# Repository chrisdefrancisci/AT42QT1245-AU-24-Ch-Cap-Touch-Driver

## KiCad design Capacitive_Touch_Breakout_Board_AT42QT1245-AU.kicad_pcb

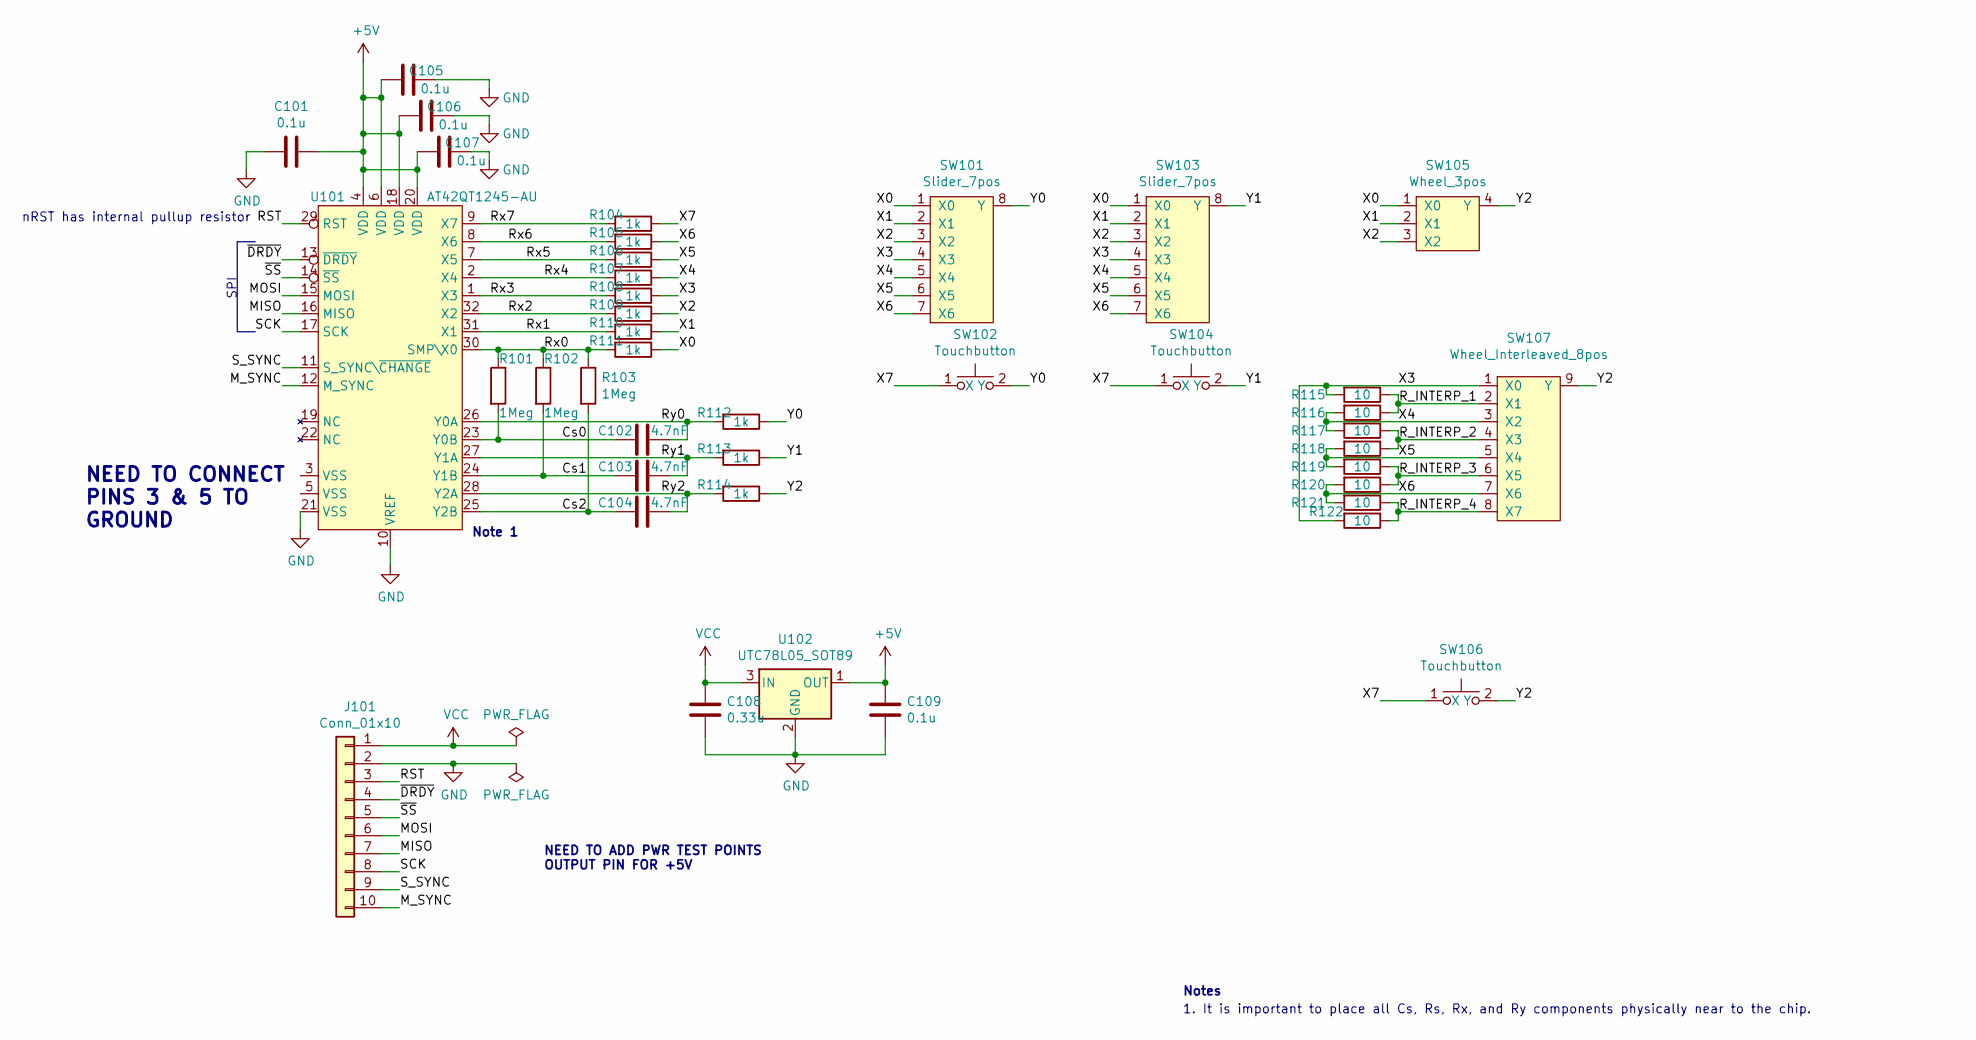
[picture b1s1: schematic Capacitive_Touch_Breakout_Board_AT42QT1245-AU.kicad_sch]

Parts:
C101, C105, C106, C107, C109: 0.1u; C_0402_1005Metric; JLCPCB Part # C307331
C102, C103, C104: 4.7nF; C_0402_1005Metric; JLCPCB Part # C1538
C108: 0.33u; C_0805_2012Metric; JLCPCB Part # C1740
J101: Conn_01x10; PinHeader_1x10_P2.54mm_Vertical
R101, R102, R103: 1Meg; R_0402_1005Metric; JLCPCB Part # C26083
R104, R105, R106, R107, R108, R109, R110, R111, R112, R113, R114: 1k; R_0402_1005Metric; JLCPCB Part # C11702
R115, R116, R117, R118, R119, R120, R121, R122: 10; R_0603_1608Metric; JLCPCB Part # C22859
SW101: Slider_7pos; Slider_Flooded_H12mm_W84mm_7pos
SW102, SW104: Touchbutton; Button_Interleaved_D12mm_P0.5mm
SW103: Slider_7pos; Slider_Interleaved_H12mm_W72mm_7pos
SW105: Wheel_3pos; Wheel_Flooded_R13mm
SW106: Touchbutton; Button_Flooded_D12
SW107: Wheel_Interleaved_8pos; Wheel_Interleaved_R17mm
U101: AT42QT1245-AU; TQFP-32_7x7mm_P0.8mm
U102: UTC78L05_SOT89; SOT-89-3; JLCPCB Part # C71136

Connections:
+5V: C101.1, C105.2, C106.2, C107.2, C109.1, U101.4 (VDD), U101.6 (VDD), U101.18 (VDD), U101.20 (VDD), U102.1 (OUT)
/Cs0: C102.2, R101.2, U101.23 (Y0B)
/Cs1: C103.2, R102.2, U101.24 (Y1B)
/Cs2: C104.2, R103.2, U101.25 (Y2B)
/MISO: J101.7, U101.16 (MISO)
/MOSI: J101.6, U101.15 (MOSI)
/M_SYNC: J101.10, U101.12 (M_SYNC)
/RST: J101.3, U101.29 (RST)
/R_INTERP_1: R115.1, R116.1, SW107.2 (X1)
/R_INTERP_2: R117.1, R118.1, SW107.4 (X3)
/R_INTERP_3: R119.1, R120.1, SW107.6 (X5)
/R_INTERP_4: R121.1, R122.1, SW107.8 (X7)
/Rx0: R101.1, R102.1, R103.1, R111.2, U101.30 (SMP\X0)
/Rx1: R110.2, U101.31 (X1)
/Rx2: R109.2, U101.32 (X2)
/Rx3: R108.2, U101.1 (X3)
/Rx4: R107.2, U101.2 (X4)
/Rx5: R106.2, U101.7 (X5)
/Rx6: R105.2, U101.8 (X6)
/Rx7: R104.2, U101.9 (X7)
/Ry0: C102.1, R112.2, U101.26 (Y0A)
/Ry1: C103.1, R113.2, U101.27 (Y1A)
/Ry2: C104.1, R114.2, U101.28 (Y2A)
/SCK: J101.8, U101.17 (SCK)
/S_SYNC: J101.9, U101.11 (S_SYNC\~CHANGE)
/X0: R111.1, SW101.1 (X0), SW103.1 (X0), SW105.1 (X0)
/X1: R110.1, SW101.2 (X1), SW103.2 (X1), SW105.2 (X1)
/X2: R109.1, SW101.3 (X2), SW103.3 (X2), SW105.3 (X2)
/X3: R108.1, R115.2, R122.2, SW101.4 (X3), SW103.4 (X3), SW107.1 (X0)
/X4: R107.1, R116.2, R117.2, SW101.5 (X4), SW103.5 (X4), SW107.3 (X2)
/X5: R106.1, R118.2, R119.2, SW101.6 (X5), SW103.6 (X5), SW107.5 (X4)
/X6: R105.1, R120.2, R121.2, SW101.7 (X6), SW103.7 (X6), SW107.7 (X6)
/X7: R104.1, SW102.1 (X), SW104.1 (X), SW106.1 (X)
/Y0: R112.1, SW101.8 (Y), SW102.2 (Y)
/Y1: R113.1, SW103.8 (Y), SW104.2 (Y)
/Y2: R114.1, SW105.4 (Y), SW106.2 (Y), SW107.9 (Y)
/~DRDY: J101.4, U101.13 (~DRDY)
/~SS: J101.5, U101.14 (~SS)
GND: C101.2, C105.1, C106.1, C107.1, C108.2, C109.2, J101.2, U101.10 (VREF), U101.21 (VSS), U102.2 (GND)
VCC: C108.1, J101.1, U102.3 (IN)

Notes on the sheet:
NEED TO ADD PWR TEST POINTS OUTPUT PIN FOR +5V
NEED TO CONNECT PINS 3 & 5 TO GROUND
Note 1
SPI
1. It is important to place all Cs, Rs, Rx, and Ry components physically near to the chip.
Notes
nRST has internal pullup resistor

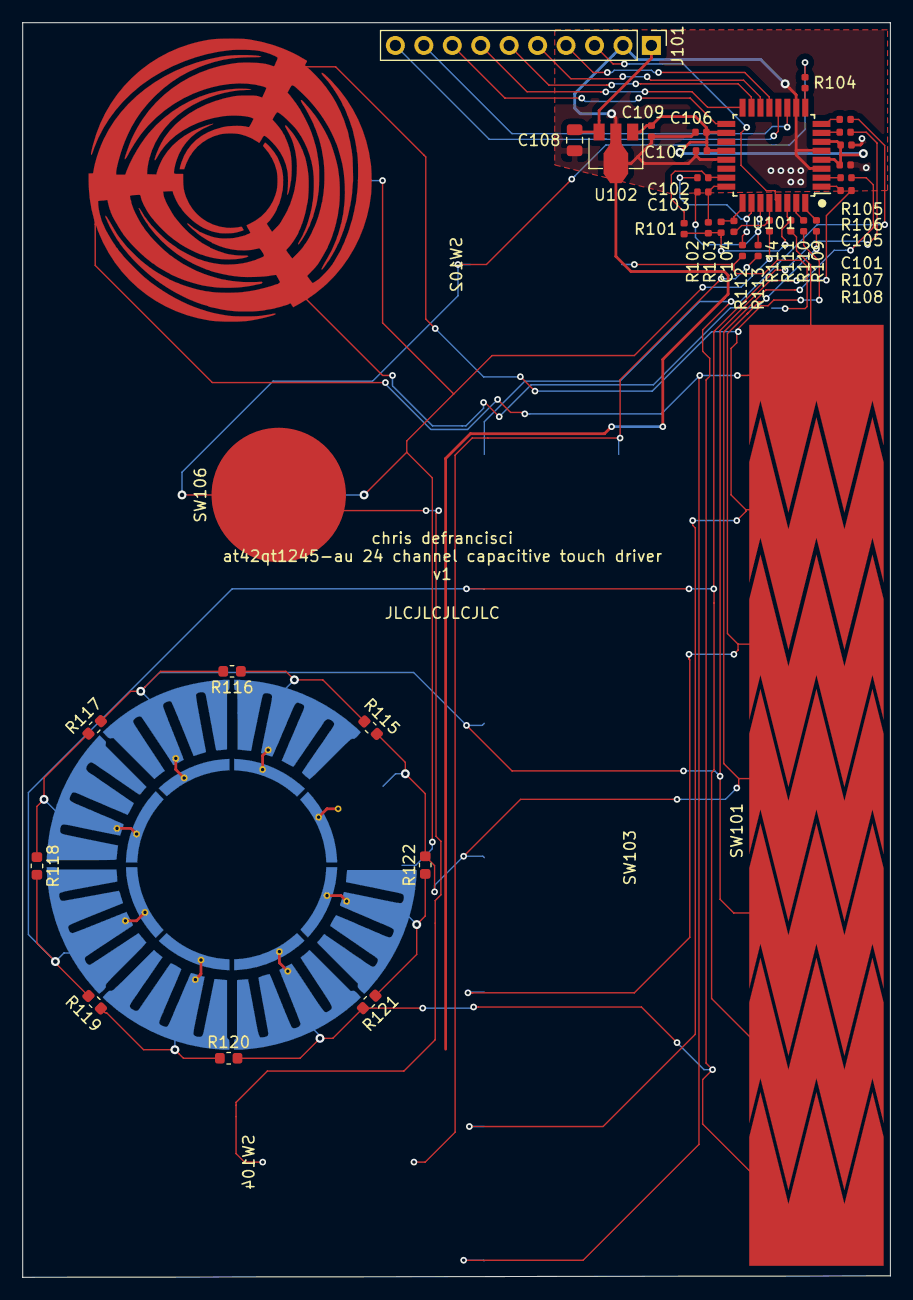
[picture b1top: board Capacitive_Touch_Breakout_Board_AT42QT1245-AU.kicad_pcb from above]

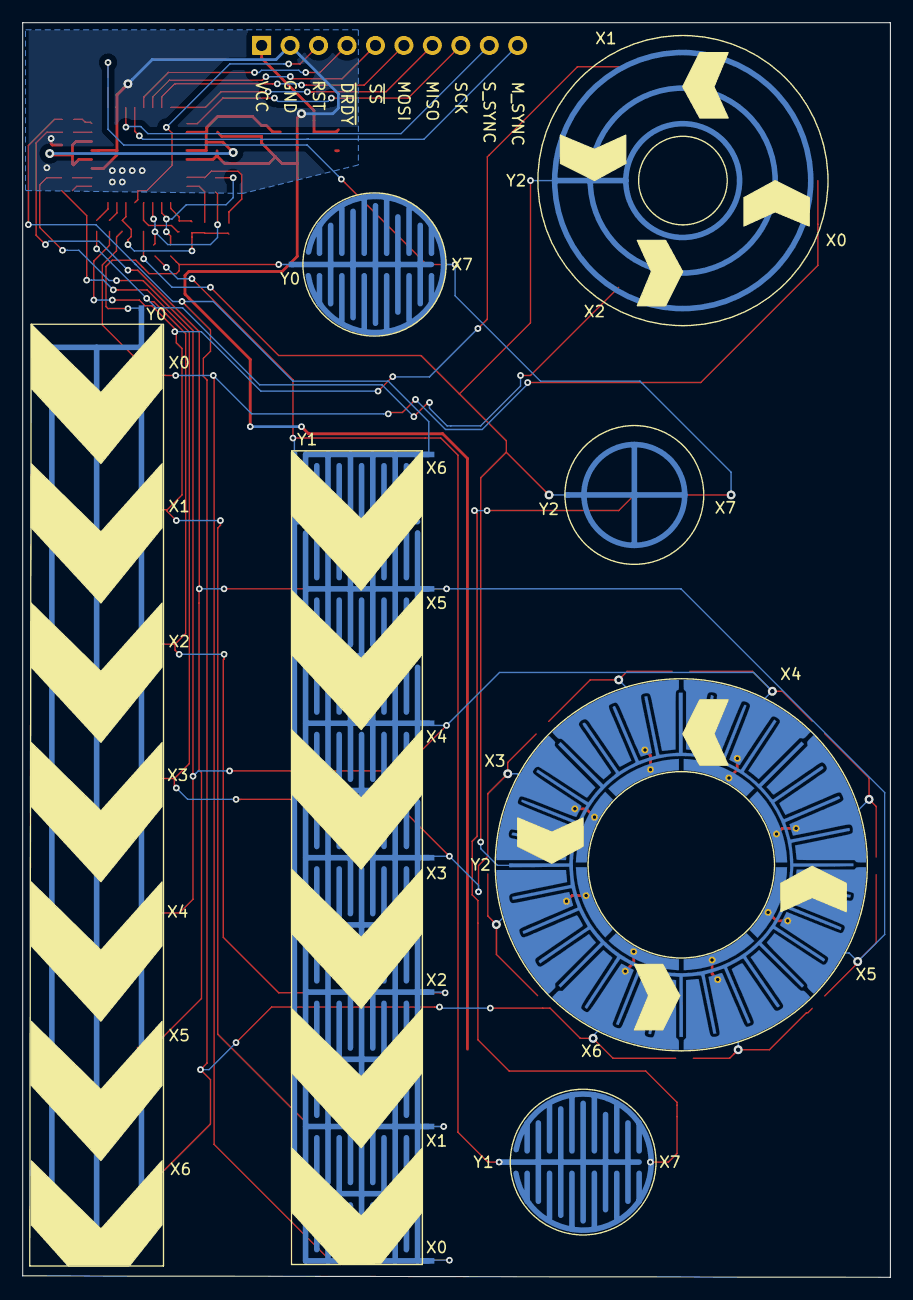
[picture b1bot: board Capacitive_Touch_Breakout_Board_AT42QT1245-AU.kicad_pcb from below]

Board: 2 copper layers, 77.5 x 112.0 mm, 41 parts (5 on the bottom side), 40 nets.

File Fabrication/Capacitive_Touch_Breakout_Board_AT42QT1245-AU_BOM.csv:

Comment,Designator,Footprint,LCSC Part Number
"0.1u","C101,C105,C106,C107,C109","Capacitor_SMD:C_0402_1005Metric",""
"4.7nF","C102,C103,C104","Capacitor_SMD:C_0402_1005Metric",""
"0.33u","C108","Capacitor_SMD:C_0805_2012Metric",""
"Conn_01x10","J101","Connector_PinHeader_2.54mm:PinHeader_1x10_P2.54mm_Vertical",""
"1Meg","R101,R102,R103","Resistor_SMD:R_0402_1005Metric",""
"1k","R104,R105,R106,R107,R108,R109,R110,R111,R112,R113,R114","Resistor_SMD:R_0402_1005Metric",""
"10","R115,R116,R117,R118,R119,R120,R121,R122","Resistor_SMD:R_0603_1608Metric",""
"Slider_7pos","SW101","Button_Slider_Capacitive:Slider_Flooded_H12mm_W84mm_7pos",""
"Touchbutton","SW102,SW104","Button_Slider_Capacitive:Button_Interleaved_D12mm_P0.5mm",""
"Slider_7pos","SW103","Button_Slider_Capacitive:Slider_Interleaved_H12mm_W72mm_7pos",""
"Wheel_3pos","SW105","Button_Slider_Capacitive:Wheel_Flooded_R13mm",""
"Touchbutton","SW106","Button_Slider_Capacitive:Button_Flooded_D12",""
"Wheel_Interleaved_8pos","SW107","Button_Slider_Capacitive:Wheel_Interleaved_R17mm",""
"AT42QT1245-AU","U101","Package_QFP:TQFP-32_7x7mm_P0.8mm",""
"UTC78L05_SOT89","U102","Package_TO_SOT_SMD:SOT-89-3",""

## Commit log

2022-06-25 Commit of first version
2022-07-08 Annotations, ran ERC, fixed net Ry0 connected to Cs1 bug
